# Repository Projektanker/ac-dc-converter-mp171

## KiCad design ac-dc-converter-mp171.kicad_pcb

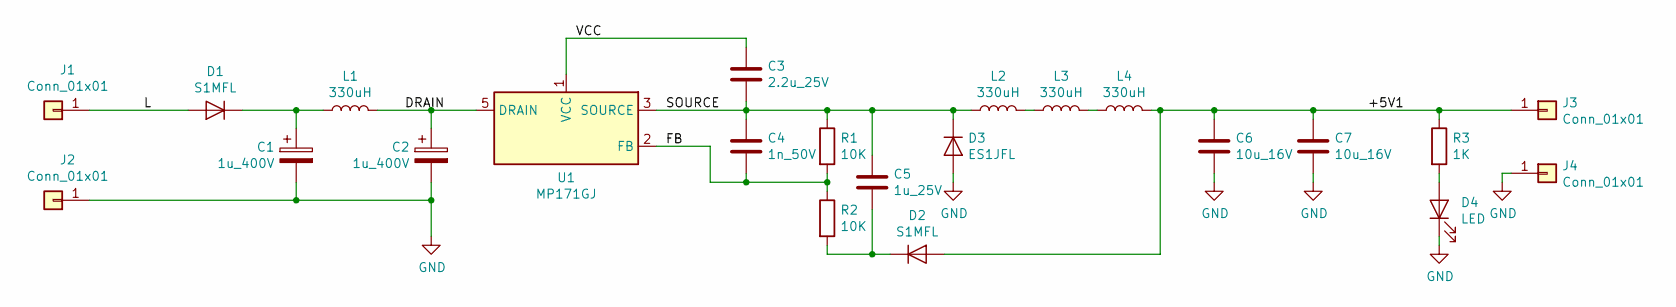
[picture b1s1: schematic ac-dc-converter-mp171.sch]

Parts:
C1, C2: 1u_400V; CP_Radial_D6.3mm_P2.50mm
C3: 2.2u_25V; C_0805_2012Metric
C4: 1n_50V; C_0603_1608Metric
C5: 1u_25V; C_0805_2012Metric
C6, C7: 10u_16V; C_0805_2012Metric
D1, D2: S1MFL; D_SOD-123F; MPN S1MFL
D3: ES1JFL; D_SOD-123F; MPN ES1JFL
D4: LED; LED_0603_1608Metric
J1, J2, J3, J4: Conn_01x01; PinHeader_1x01_P2.54mm_Vertical
L1, L2, L3, L4: 330uH; L_1210_3225Metric; MPN 744032331
R1, R2: 10K; R_0603_1608Metric
R3: 1K; R_0603_1608Metric
U1: MP171GJ; TSOT-23-5; MPN MP171GJ-Z

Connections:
/+5V1: C6.1, C7.1, D2.2 (A), J3.1, L4.2, R3.1
/DRAIN: C2.1, L1.2, U1.5 (DRAIN)
/FB: C4.2, R1.2, R2.1, U1.2 (FB)
/L: D1.2 (A), J1.1
/SOURCE: C3.2, C4.1, C5.1, D3.1 (K), L2.1, R1.1, U1.3 (SOURCE), U1.4 (SOURCE)
/VCC: C3.1, U1.1 (VCC)
GND: C1.2, C2.2, C6.2, C7.2, D3.2 (A), D4.1 (K), J2.1, J4.1
unnamed: C1.1, D1.1 (K), L1.1
unnamed: C5.2, D2.1 (K), R2.2
unnamed: D4.2 (A), R3.2
unnamed: L2.2, L3.1
unnamed: L3.2, L4.1

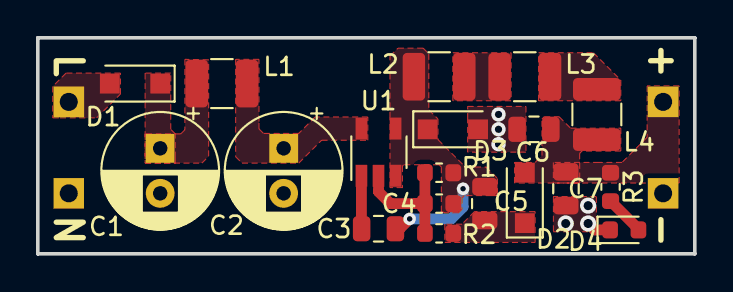
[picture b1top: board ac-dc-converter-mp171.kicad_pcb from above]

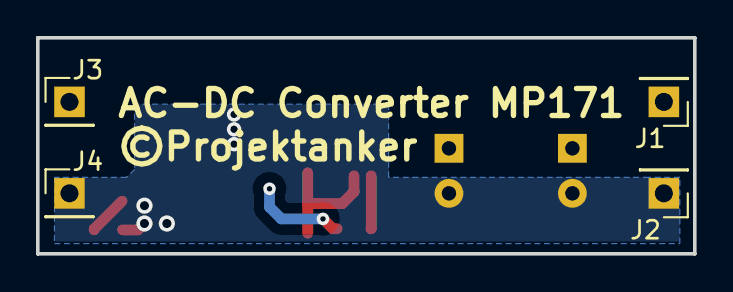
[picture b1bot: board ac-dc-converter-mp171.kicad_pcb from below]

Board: 2 copper layers, 36.5 x 12.0 mm, 23 parts (4 on the bottom side), 12 nets.

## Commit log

2019-03-04 Renamed project
2019-03-05 completed so far. ready to order.

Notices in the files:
ac-dc-converter-mp171.kicad_pcb:
©Projektanker
